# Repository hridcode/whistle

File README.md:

# Whistle

Whistle is the devboard of all time. It shares many similarities with the Raspberry Pi Pico, having the RP2040 SoC on board. However, this board aims to improve on the Pico's shortcomings. No more dealing with the haunting micro-USB port! This board uses a USB-C connection port. It also has 1 extra ADC pin, as well as an inbuilt digital-to-analog converter (DAC) and mono speaker amplifier, making it perfect for audio-integrated projects!

Oh, I almost forgot, it has LiPo battery charging!

# Photos

|Schematic|PCB|3D Render|
|---|---|---|
||||

# BOM

|Item|Cost|Source|
|---|---|---|
|RP2040|$0.94|https://www.lcsc.com/product-detail/C2040.html?s_z=s_p_RP2040&spm=wm.ssy.bg.0.xh&lcsc_vid=E1ENUAdXFlVdBAVSQFBZUQJQRFEMVgIFEgVcAgBRQgQxVlNRQFNbUVBfR1haUjsOAxUeFF5JWBYZEEoKFBINSQcJGk4%3D|
|Crystal oscillator|$0.07|https://www.lcsc.com/product-detail/C9002.html?s_z=s_q_CRYSTAL%252012MHZ&spm=wm.ssy.bg.0.xh&lcsc_vid=E1ENUAdXFlVdBAVSQFBZUQJQRFEMVgIFEgVcAgBRQgQxVlNRQFNbUVFTRlVXXzsOAxUeFF5JWBYZEEoKFBINSQcJGk4eFQsCAgIaSgADAwAHC0slRVFaV0oOAwwC|
|MCP1700 LDO, 3.3V|$0.98|https://www.lcsc.com/product-detail/C39051.html?s_z=n_q_mcp1700%2520tt&spm=wm.ssy.bg.16.xh&lcsc_vid=E1ENUAdXFlVdBAVSQFBZUQJQRFEMVgIFEgVcAgBRQgQxVlNRQFNbUVJRR1hcXjsOAxUeFF5JWBYZEEoKFBINSQcJGk4dAgUUFAk%3D|
|USB-C port, 16-pin|$0.08|https://www.lcsc.com/product-detail/C2988369.html?s_z=n_q_usb%2520c%252016&spm=wm.ssy.bg.0.xh&lcsc_vid=E1ENUAdXFlVdBAVSQFBZUQJQRFEMVgIFEgVcAgBRQgQxVlNRQFNbUVNSRVVYVzsOAxUeFF5JWBYZEEoKFBINSQcJGk4eFQsCAgIaSgADAwAHC0slRFheUlVIHxUDCw%3D%3D|
|W25Q128JVSIQ flash memory|$1.96|https://www.lcsc.com/product-detail/C97521.html?s_z=s_q_W25Q128JVSIQ&spm=wm.ssy.bg.0.xh&lcsc_vid=E1ENUAdXFlVdBAVSQFBZUQJQRFEMVgIFEgVcAgBRQgQxVlNRQFNbUVxWRFlWVTsOAxUeFF5JWBYZEEoKFBINSQcJGk4eFQsCAgIaSgADAwAHC0slRVhWX1dQTk8GEwkK|
|PCM5102A DAC|$1.02|https://www.lcsc.com/product-detail/C107671.html?s_z=n_q_pcm5102a&spm=wm.ssy.bg.1.xh&lcsc_vid=E1ENUAdXFlVdBAVSQFBZUQJQRFEMVgIFEgVcAgBRQgQxVlNRQFNbUV1XRVlaVjsOAxUeFF5JWBYZEEoKFBINSQcJGk4dAgUUFAk%3D|
|PAM8302AAD speaker amplifier|$0.21|https://www.lcsc.com/product-detail/C112137.html?s_z=n_q_pam8302aad&spm=wm.ssy.bg.0.xh&lcsc_vid=E1ENUAdXFlVdBAVSQFBZUQJQRFEMVgIFEgVcAgBRQgQxVlNRQFNbUV1SQFJbUzsOAxUeFF5JWBYZEEoKFBINSQcJGk4eFQsCAgIaSgADAwAHC0slRlFZUVNXWQkaCgg%3D|
|BQ25185 battery charging IC|$1.66|https://www.lcsc.com/product-detail/C19725033.html?s_z=s_p_BQ25185DLHR&spm=wm.ssy.bg.0.xh&lcsc_vid=E1ENUAdXFlVdBAVSQFBZUQJQRFEMVgIFEgVcAgBRQgQxVlNRQFNbUV1fQ1RWVzsOAxUeFF5JWBYZEEoKFBINSQcJGk4eFQsCAgIaSgADAwAHC0slRlBcVldRWQkaCgg%3D|
|SMD tactile switch, 6x6mm|$0.03|https://www.lcsc.com/product-detail/C49234152.html?s_z=n_q_5x5mm%2520button&spm=wm.ssy.bg.0.xh&lcsc_vid=RlQIVAdXEVQKUwJREwNdVlQAEQNaUAUCTlNbAgdURlMxVlNRQFJcUFFUTlhdUDsOAxUeFF5JWBYZEEoKFBINSQcJGk4%3D|
|Pin headers|$0.38|https://www.lcsc.com/product-detail/C2938459.html?s_z=h_q_pin%2520headers%252001x20&spm=wm.ssy.bg.1.xh&lcsc_vid=RlQIVAdXEVQKUwJREwNdVlQAEQNaUAUCTlNbAgdURlMxVlNRQFJcX1dVQFdZVTsOAxUeFF5JWBYZEEoKFBINSQcJGk4eFQsCAgIaSgADAwAHC0slRVhdX1BUQ08GEwkK|
|PCB|$0.42|https://cart.jlcpcb.com/quote?stencilLayer=2&stencilWidth=21&stencilLength=54&stencilCounts=5&plateType=1|
|Stencil|$3.05|https://cart.jlcpcb.com/quote?stencilLayer=2&stencilWidth=21&stencilLength=54&stencilCounts=5&plateType=1|

Total: $10.81 ($7.76 w/o stencil)

# Notes

Have fun!

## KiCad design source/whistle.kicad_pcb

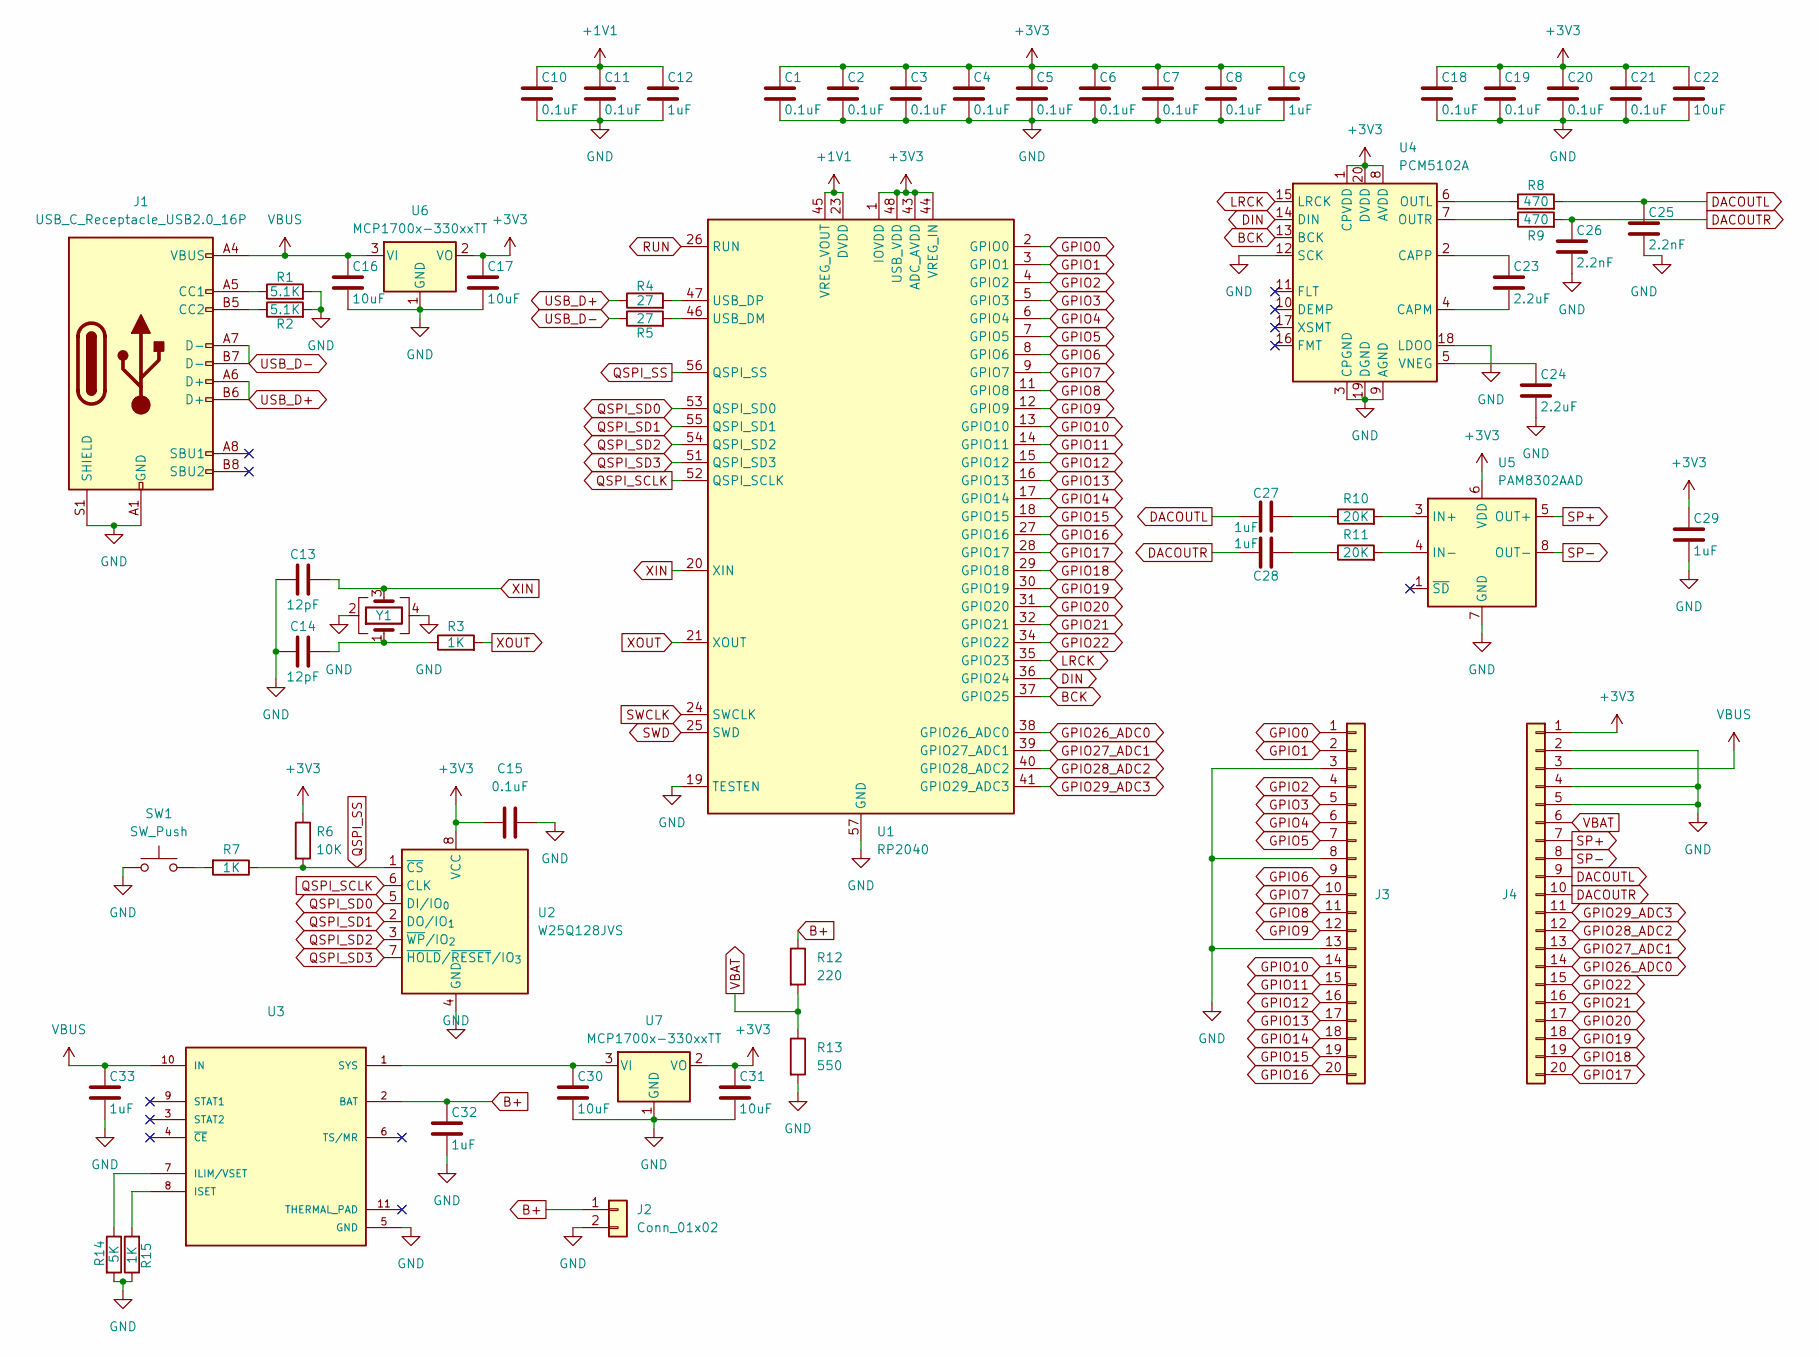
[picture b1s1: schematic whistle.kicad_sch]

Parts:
C1, C2, C3, C4, C5, C6, C7, C8, C10, C11, C15, C18, C19, C20, C21: 0.1uF; C_0402_1005Metric
C9, C12, C27, C28, C29, C32, C33: 1uF; C_0402_1005Metric
C13, C14: 12pF; C_0402_1005Metric
C16, C17, C22, C30, C31: 10uF; C_0402_1005Metric
C23, C24: 2.2uF; C_0402_1005Metric
C25, C26: 2.2nF; C_0402_1005Metric
J1: USB_C_Receptacle_USB2.0_16P; USB_C_Receptacle_HRO_TYPE-C-31-M-12
J2: Conn_01x02; JST_EH_B2B-EH-A_1x02_P2.50mm_Vertical
J3, J4: Conn_01x20; PinHeader_1x20_P2.54mm_Vertical
R1, R2: 5.1K; R_0402_1005Metric_Pad0.72x0.64mm_HandSolder
R3, R7, R15: 1K; R_0402_1005Metric_Pad0.72x0.64mm_HandSolder
R4, R5: 27; R_0402_1005Metric_Pad0.72x0.64mm_HandSolder
R6: 10K; R_0402_1005Metric_Pad0.72x0.64mm_HandSolder
R8, R9: 470; R_0402_1005Metric_Pad0.72x0.64mm_HandSolder
R10, R11: 20K; R_0402_1005Metric_Pad0.72x0.64mm_HandSolder
R12: 220; R_0402_1005Metric_Pad0.72x0.64mm_HandSolder
R13: 550; R_0402_1005Metric_Pad0.72x0.64mm_HandSolder
R14: 5K; R_0402_1005Metric_Pad0.72x0.64mm_HandSolder
SW1: SW_Push; SW_SPST_PTS647_Sx50
U1: RP2040; QFN-56-1EP_7x7mm_P0.4mm_EP3.2x3.2mm
U2: W25Q128JVS; SOIC-8_5.3x5.3mm_P1.27mm
U3: WSON-10-1EP_4x3mm_P0.5mm_EP2.2x2mm
U4: PCM5102A; TSSOP-20_4.4x6.5mm_P0.65mm
U5: PAM8302AAD; MSOP-8-1EP_3x3mm_P0.65mm_EP1.5x1.8mm_ThermalVias
U6, U7: MCP1700x-330xxTT; SOT-23
Y1: Crystal_GND24; Crystal_SMD_1210-4Pin_1.2x1.0mm

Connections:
+1V1: C10.1, C11.1, C12.1, U1.23 (DVDD), U1.45 (VREG_VOUT), U1.50 (DVDD)
+3V3: C1.1, C2.1, C3.1, C4.1, C5.1, C6.1, C7.1, C8.1, C9.1, C15.1, C17.1, C18.1, C19.1, C20.1, C21.1, C22.1, C29.1, C31.1, J4.1, R6.1, U1.1 (IOVDD), U1.10 (IOVDD), U1.22 (IOVDD), U1.33 (IOVDD), U1.42 (IOVDD), U1.43 (ADC_AVDD), U1.44 (VREG_IN), U1.48 (USB_VDD), U1.49 (IOVDD), U2.8 (VCC), U4.1 (CPVDD), U4.8 (AVDD), U4.20 (DVDD), U5.6 (VDD), U6.2 (VO), U7.2 (VO)
B+: C32.1, J2.1, R12.1, U3.2 (BAT)
BCK: U1.37 (GPIO25), U4.13 (BCK)
DACOUTL: C25.1, C27.1, J4.9, R8.2
DACOUTR: C26.1, C28.2, J4.10, R9.2
DIN: U1.36 (GPIO24), U4.14 (DIN)
GPIO0: J3.1, U1.2 (GPIO0)
GPIO1: J3.2, U1.3 (GPIO1)
GPIO2: J3.4, U1.4 (GPIO2)
GPIO3: J3.5, U1.5 (GPIO3)
GPIO4: J3.6, U1.6 (GPIO4)
GPIO5: J3.7, U1.7 (GPIO5)
GPIO6: J3.9, U1.8 (GPIO6)
GPIO7: J3.10, U1.9 (GPIO7)
GPIO8: J3.11, U1.11 (GPIO8)
GPIO9: J3.12, U1.12 (GPIO9)
GPIO10: J3.14, U1.13 (GPIO10)
GPIO11: J3.15, U1.14 (GPIO11)
GPIO12: J3.16, U1.15 (GPIO12)
GPIO13: J3.17, U1.16 (GPIO13)
GPIO14: J3.18, U1.17 (GPIO14)
GPIO15: J3.19, U1.18 (GPIO15)
GPIO16: J3.20, U1.27 (GPIO16)
GPIO17: J4.20, U1.28 (GPIO17)
GPIO18: J4.19, U1.29 (GPIO18)
GPIO19: J4.18, U1.30 (GPIO19)
GPIO20: J4.17, U1.31 (GPIO20)
GPIO21: J4.16, U1.32 (GPIO21)
GPIO22: J4.15, U1.34 (GPIO22)
GPIO26_ADC0: J4.14, U1.38 (GPIO26_ADC0)
GPIO27_ADC1: J4.13, U1.39 (GPIO27_ADC1)
GPIO28_ADC2: J4.12, U1.40 (GPIO28_ADC2)
GPIO29_ADC3: J4.11, U1.41 (GPIO29_ADC3)
LRCK: U1.35 (GPIO23), U4.15 (LRCK)
unnamed: C14.2, R3.1, Y1.1
unnamed: C27.2, R10.1
unnamed: C28.1, R11.1
unnamed: J1.A5 (CC1), R1.1
unnamed: J1.B5 (CC2), R2.1
unnamed: R7.2, SW1.2
unnamed: R5.2, U1.46 (USB_DM)
unnamed: R4.2, U1.47 (USB_DP)
unnamed: R14.1, U3.7 (ILIM/VSET)
unnamed: R15.2, U3.8 (ISET)
unnamed: C30.1, U3.1 (SYS), U7.3 (VI)
unnamed: C23.2, U4.4 (CAPM)
unnamed: C23.1, U4.2 (CAPP)
unnamed: R8.1, U4.6 (OUTL)
unnamed: R9.1, U4.7 (OUTR)
unnamed: R10.2, U5.3 (IN+)
unnamed: R11.2, U5.4 (IN-)
QSPI_SCLK: U1.52 (QSPI_SCLK), U2.6 (CLK)
QSPI_SD0: U1.53 (QSPI_SD0), U2.5 (DI/IO_{0})
QSPI_SD1: U1.55 (QSPI_SD1), U2.2 (DO/IO_{1})
QSPI_SD2: U1.54 (QSPI_SD2), U2.3 (~WP/IO_{2})
QSPI_SD3: U1.51 (QSPI_SD3), U2.7 (~HOLD/~RESET/IO_{3})
QSPI_SS: R6.2, R7.1, U1.56 (QSPI_SS), U2.1 (~CS)
RUN: U1.26 (RUN)
SP+: J4.7, U5.5 (OUT+)
SP-: J4.8, U5.8 (OUT-)
SWCLK: U1.24 (SWCLK)
SWD: U1.25 (SWD)
USB_D+: J1.A6 (D+), J1.B6 (D+), R4.1
USB_D-: J1.A7 (D-), J1.B7 (D-), R5.1
VBAT: J4.6, R12.2, R13.1
VBUS: C16.1, C33.1, J1.A4 (VBUS), J1.A9 (VBUS), J1.B4 (VBUS), J1.B9 (VBUS), J4.3, U3.10 (IN), U6.3 (VI)
XIN: C13.2, U1.20 (XIN), Y1.3
XOUT: R3.2, U1.21 (XOUT)

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
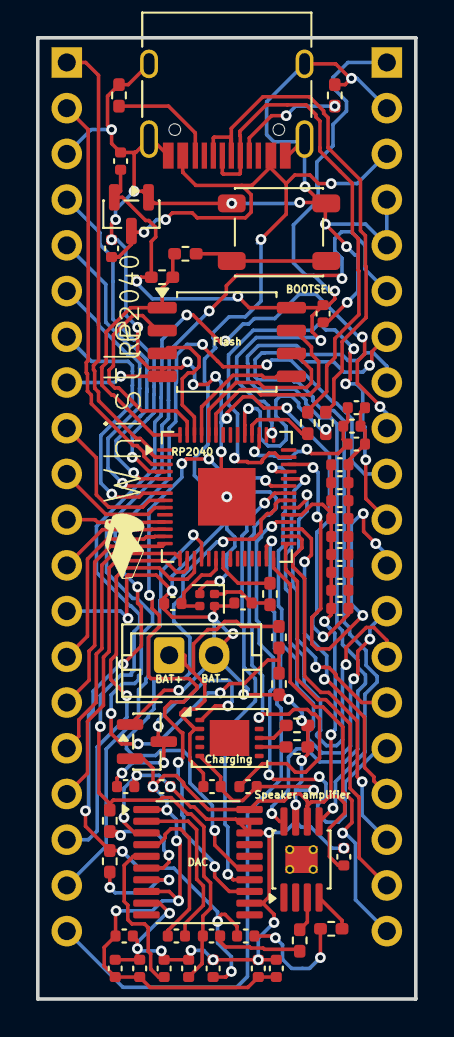
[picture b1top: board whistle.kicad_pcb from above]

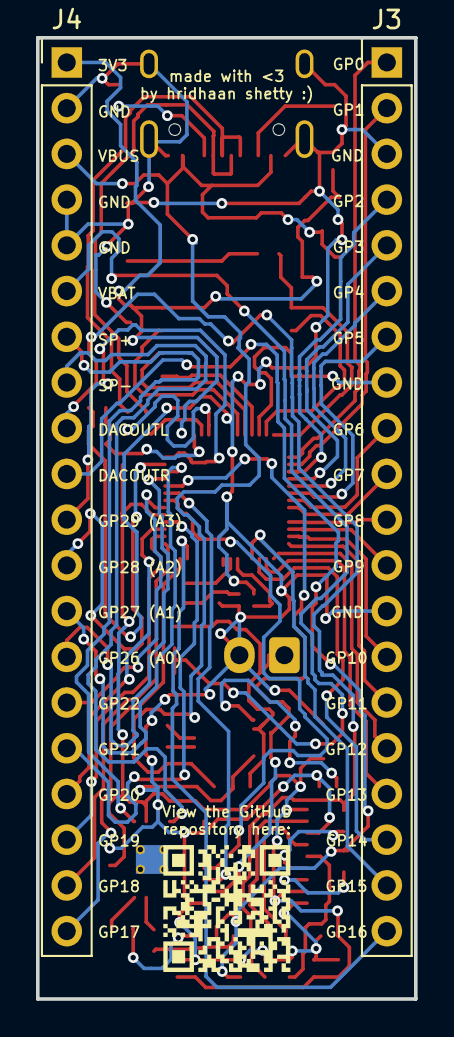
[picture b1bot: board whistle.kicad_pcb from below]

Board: 2 copper layers, 21.0 x 53.4 mm, 61 parts (2 on the bottom side), 68 nets.

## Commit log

2026-04-27 Added production, source, BOM and updated README.md
2026-04-27 Added photos
2026-04-27 Updated BOM
